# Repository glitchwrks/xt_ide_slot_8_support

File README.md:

# Slot 8 Support for the XT-IDE 8-Bit IDE Controller

[Glitch Works](http://www.glitchwrks.com/) daughterboard for Slot 8 Support on the XT-IDE. This module can be used with any XT-IDE that includes ISA pin `B8`, which is all [rev 3](http://www.glitchwrks.com/2016/07/06/xt-ide-rev3) boards, most rev 2 boards, and early rev 1 boards. Production rev 1 boards (2009-2010 era) had `B8` removed to reduce cost, and can't use this module

More info on the Glitch Works project to provide XT-IDE related boards, kits, and fully assembled units [can be found here](http://www.glitchwrks.com/xt-ide). A writeup on the Slot 8 Support design process [is available here](http://www.glitchwrks.com/2017/02/03/slot-8-support).

### Versions

Originally there were two sets of Gerber files for this project, one with silkscreen legends, and one where the legend was done as solder mask relief. I've since dropped the silkscreened version since the "nosilk" version can be run at any board house, even those with lousy silkscreen quality. Here's the current production board, with castellated mounting holes:

This version is 100% functional and the Gerbers can be submitted directly to OSH Park. You'll receive a board with [castellated holes](http://docs.oshpark.com/tips+tricks/castellation/) (which may require some deburring). OSH Park boards have been run and tested, and found to be completely functional.

### Bill of Materials

You can find a BOM with Mouser part numbers [here](https://github.com/glitchwrks/xt_ide_slot_8_support/blob/master/bill_of_materials.md). Pull requests with BOMs for other suppliers are welcome! Do note that you can purchase complete parts kits from [The Glitch Works](http://www.glitchwrks.com/xt-ide) in addition to bare PC boards.

### Notes on Running This Board

This is a single-sided board, but most (all?) board houses that do prototype quantities will run it as a double-sided board with nothing on the solder side. As such, be aware that you *do* need to include the solder side solder mask file -- solder masks are negative, so omitting the solder mask file when submitting to e.g. [OSH Park](https://oshpark.com) will result in a solid solder side mask, which will get in the through-holes and make assembly more difficult!

The design files for this board now specify [castellated holes](http://docs.oshpark.com/tips+tricks/castellation/) for the mounting tabs. Not all board houses can do this -- OSH Park can, and you can submit the Gerber ZIP directly to them and get a functional board.

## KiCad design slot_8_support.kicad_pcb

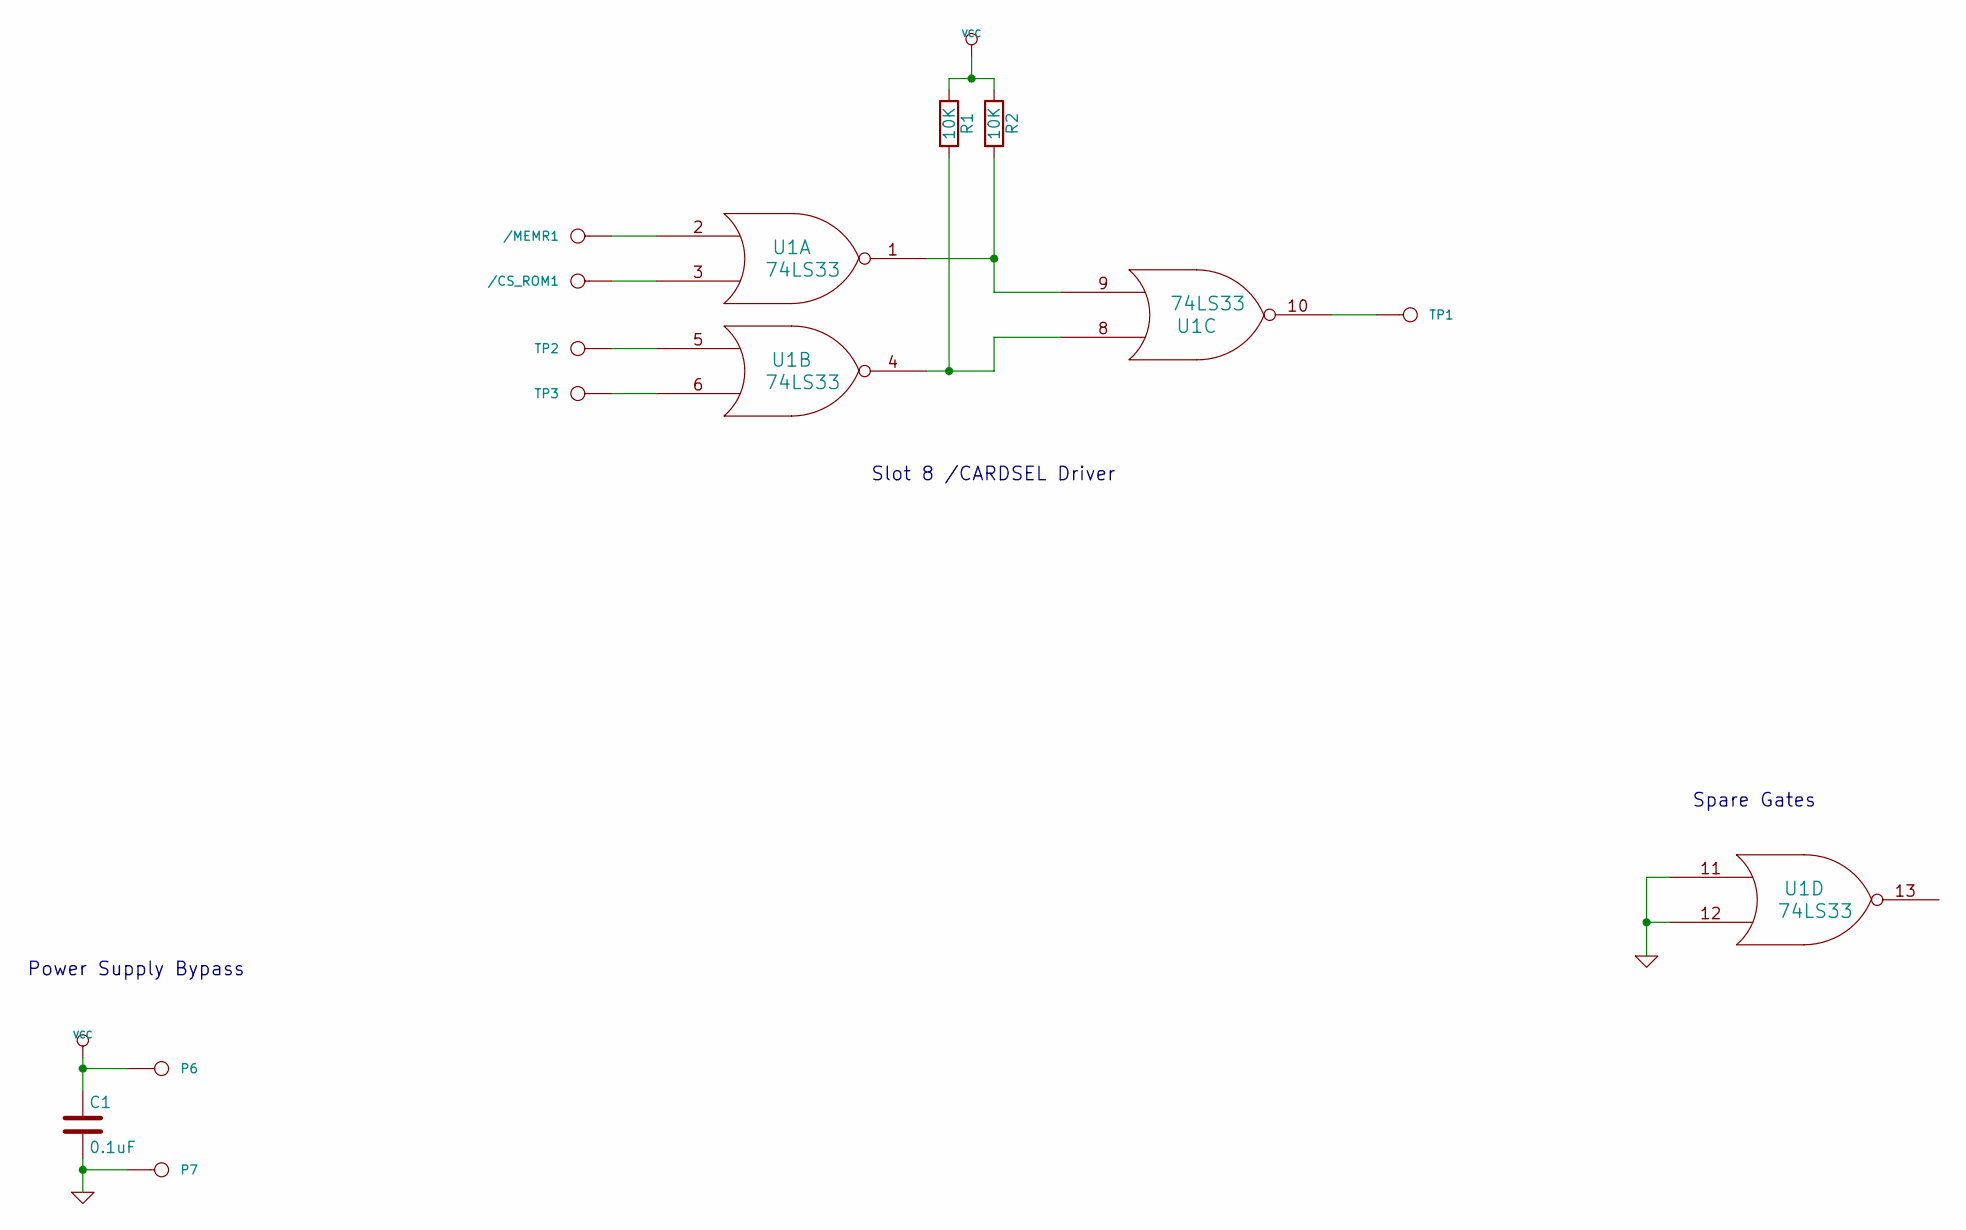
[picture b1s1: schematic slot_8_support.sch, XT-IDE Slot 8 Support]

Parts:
/CS_ROM1: CONN_1; SolderWirePad_single_0-8mmDrill
/MEMR1: CONN_1; SolderWirePad_single_0-8mmDrill
C1: 0.1uF; C_1206_HandSoldering
P6, P7: CONN_1; SolderWirePad_single_0-8mmDrill
R1, R2: 10K; R_1206_HandSoldering
TP1, TP2, TP3: CONN_1; SMD_TESTPOINT
U1: 74LS33; SOIC-14_N

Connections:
GND: C1.2, P7.1, U1.7 (GND), U1.11, U1.12
unnamed: /CS_ROM1.1, U1.3
unnamed: /MEMR1.1, U1.2
unnamed: R1.2, U1.4, U1.8
unnamed: R2.2, U1.1, U1.9
unnamed: TP1.1, U1.10
unnamed: TP2.1, U1.5
unnamed: TP3.1, U1.6
VCC: C1.1, P6.1, R1.1, R2.1, U1.14 (VCC)

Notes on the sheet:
Slot 8 /CARDSEL Driver
Power Supply Bypass
Spare Gates

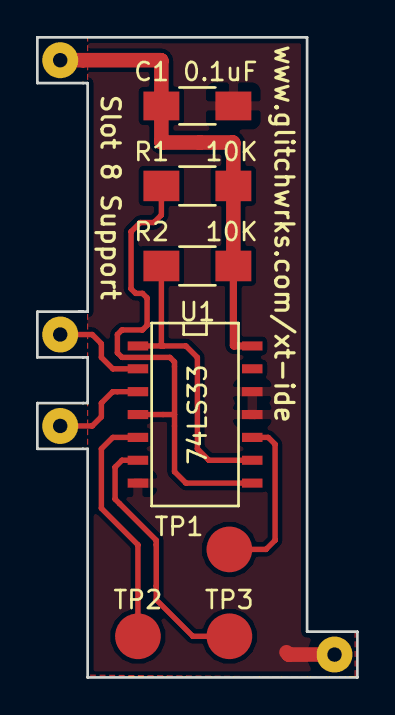
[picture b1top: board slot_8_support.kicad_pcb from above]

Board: 2 copper layers, 17.8 x 35.6 mm, 11 parts (0 on the bottom side), 9 nets.

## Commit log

2017-02-06 Removing dup Excellon drill file
2017-02-06 Adding Mouser BOM
2017-02-06 Updating README
2017-02-06 Fixing broken link in README
2017-02-06 Splitting silkscreen/nosilk boards, adding copper pour for mask relief, bottom mask layer
2017-02-06 Removing backup files
2017-02-06 Adding castellated mounting holes for nosilk version
2017-02-06 Ignoring all *bak files
2017-02-06 Removing old bak file
2017-02-21 Updating project for successful castellated hole run, removing silkscreen version
2017-02-21 Adding new Gerber rendering
